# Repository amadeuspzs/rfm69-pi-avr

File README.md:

# rfm69-pi-avr

> Work in progress.

RFM69 on a pi (hub) and AVR (node) chip.

* [RFM69 Pi Hat](hardware/pi-hat)
* [Pi Hub](hub-pi)

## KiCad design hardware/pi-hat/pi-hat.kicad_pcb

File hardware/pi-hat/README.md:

# RFM69 Pi Hat

Simple Raspberry Pi "hat" to connect an RFM69 module directly onto the GPIO of a Raspberry Pi, with SMA connector for antenna.

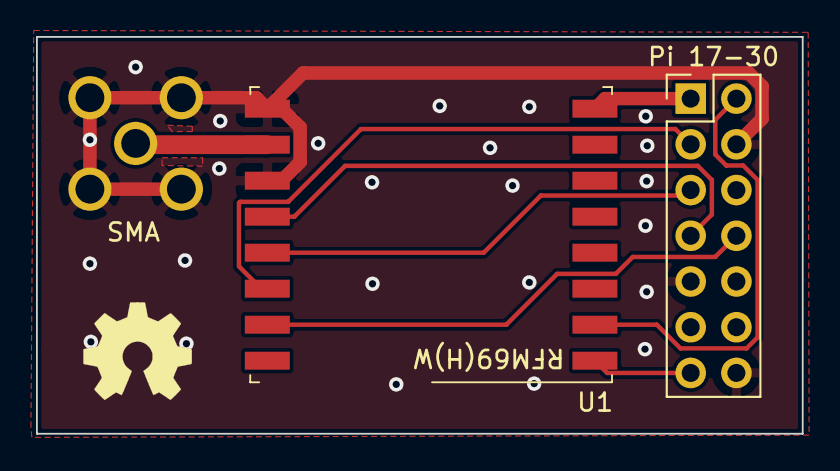
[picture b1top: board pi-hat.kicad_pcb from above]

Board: 2 copper layers, 42.5 x 22.0 mm, 3 parts (0 on the bottom side), 9 nets.

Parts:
Pi 17-30: RPi 17-26; PinHeader_2x07_P2.54mm_Vertical
SMA: 73391-0060; MOLEX_73391-0060
U1: RFM69HW; HOPERF_RFM69HW

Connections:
GND: Pi 17-30.5, Pi 17-30.8, Pi 17-30.13, SMA.2, SMA.3, SMA.4, SMA.5, U1.9, U1.11
unnamed: SMA.1, U1.10
unnamed: Pi 17-30.1, U1.8
unnamed: Pi 17-30.2, U1.14
unnamed: Pi 17-30.3, U1.13
unnamed: Pi 17-30.4, U1.12
unnamed: Pi 17-30.7, U1.1
unnamed: Pi 17-30.11, U1.15
unnamed: Pi 17-30.14, U1.2

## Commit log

2020-09-27 Add Pi code
2020-09-27 Cleanup
2020-09-27 Submodule pt2
2020-09-28 Streamlining
2020-09-28 Working code
2020-09-28 Working mqtt
2020-09-28 Simplify
2020-09-29 Add logic
2020-09-29 Working door sensor
2020-11-16 Debugging code
2020-11-16 Add test receive code
2020-11-16 Add test trasmit code
2020-11-16 Update flow
2020-11-16 Improve timeout
2020-11-16 Add debug flag
2020-11-17 Working test
2020-11-29 Add reed-switch schema
2020-11-29 Add working code
2022-04-03 Ignore kicad font cache
2022-04-03 Add pi hat
2022-04-03 Docs
2022-04-04 Add radio ping
2022-04-07 Refactor code
2022-04-07 add link to hub
2022-04-07 Linting
2022-04-07 Documentation
2022-04-07 Typos
2022-04-07 Refactor devices
2022-04-14 feat: add ultrasound sensor
2026-06-08 requirements
2026-06-08 tweak
2026-06-09 feat: working version
2026-06-14 tweaks
2026-06-21 feat: update parser
2026-06-28 battery sensor
